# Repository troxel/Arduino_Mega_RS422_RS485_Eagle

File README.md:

# Arduino_Mega_RS422_RS485_Eagle

## Eagle files for a shield for Arduinio Mega providing both RS422 and RS485 ports

Usess ttl uarts 1 and 2 to provide both RS485 and RS422 level ports. The RS485 requires setting GPIO pin 7 high to enable output and suppress imput.

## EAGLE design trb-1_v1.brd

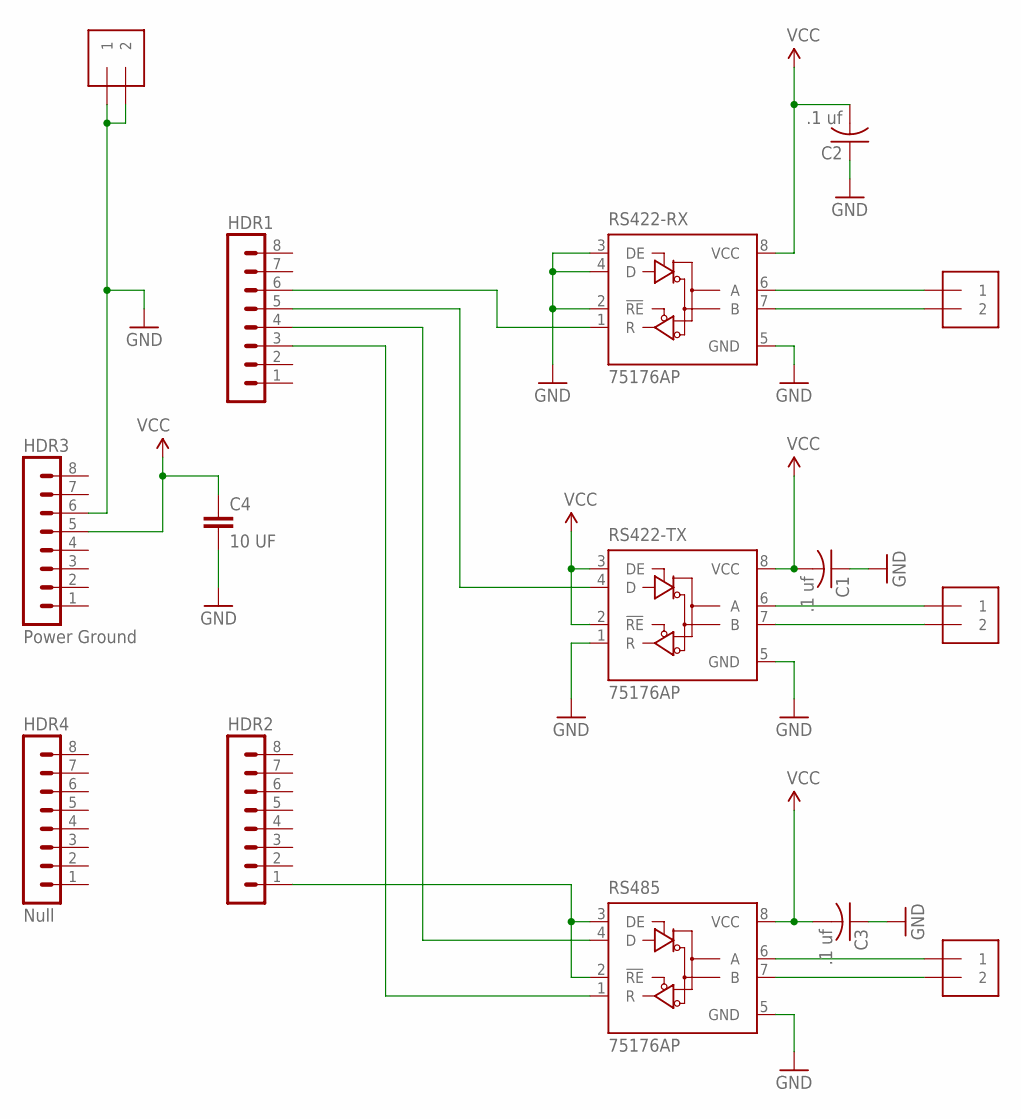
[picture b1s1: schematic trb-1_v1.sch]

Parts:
C1, C2, C3: .1 uf; C0805
C4: 10 UF; 0805-CAP
HDR1, HDR2: MA08-1
HDR3: Power Ground; MA08-1
HDR4: Null; MA08-1
J1: 1X2-3.5MM
RS422-RX, RS422-TX, RS485: 75176AP; DIL08; MPN SN75176AP
RS422-RX1, RS422-TX1, RS485-TXRX: 1X2-3.5MM

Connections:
GND: C1.1, C2.1, C3.1, C4.2, HDR3.6, J1.1, J1.2, RS422-RX.2 (!RE), RS422-RX.3 (DE), RS422-RX.4 (D), RS422-RX.5 (GND), RS422-TX.1 (R), RS422-TX.5 (GND), RS485.5 (GND)
unnamed: HDR1.3, RS485.1 (R)
unnamed: HDR1.4, RS485.4 (D)
unnamed: HDR1.5, RS422-TX.4 (D)
unnamed: HDR1.6, RS422-RX.1 (R)
unnamed: HDR2.1, RS485.2 (!RE), RS485.3 (DE)
unnamed: RS422-RX.6 (A), RS422-RX1.1
unnamed: RS422-RX.7 (B), RS422-RX1.2
unnamed: RS422-TX.6 (A), RS422-TX1.1
unnamed: RS422-TX.7 (B), RS422-TX1.2
unnamed: RS485.6 (A), RS485-TXRX.1
unnamed: RS485.7 (B), RS485-TXRX.2
VCC: C1.2, C2.2, C3.2, C4.1, HDR3.5, RS422-RX.8 (VCC), RS422-TX.2 (!RE), RS422-TX.3 (DE), RS422-TX.8 (VCC), RS485.8 (VCC)

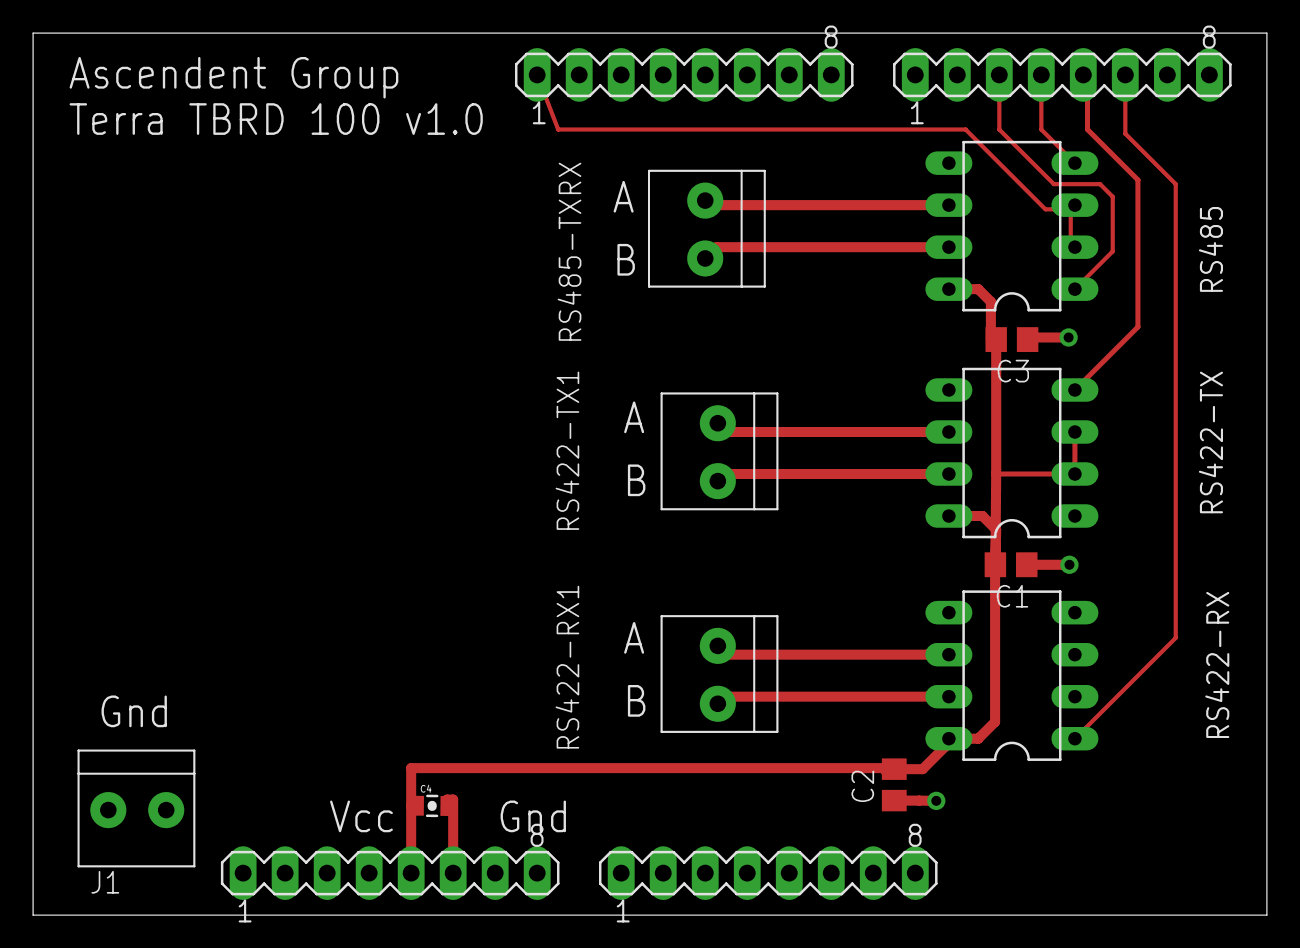
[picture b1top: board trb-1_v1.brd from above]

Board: 2 copper layers, 74.6 x 53.3 mm, 15 parts (0 on the bottom side), 13 nets.

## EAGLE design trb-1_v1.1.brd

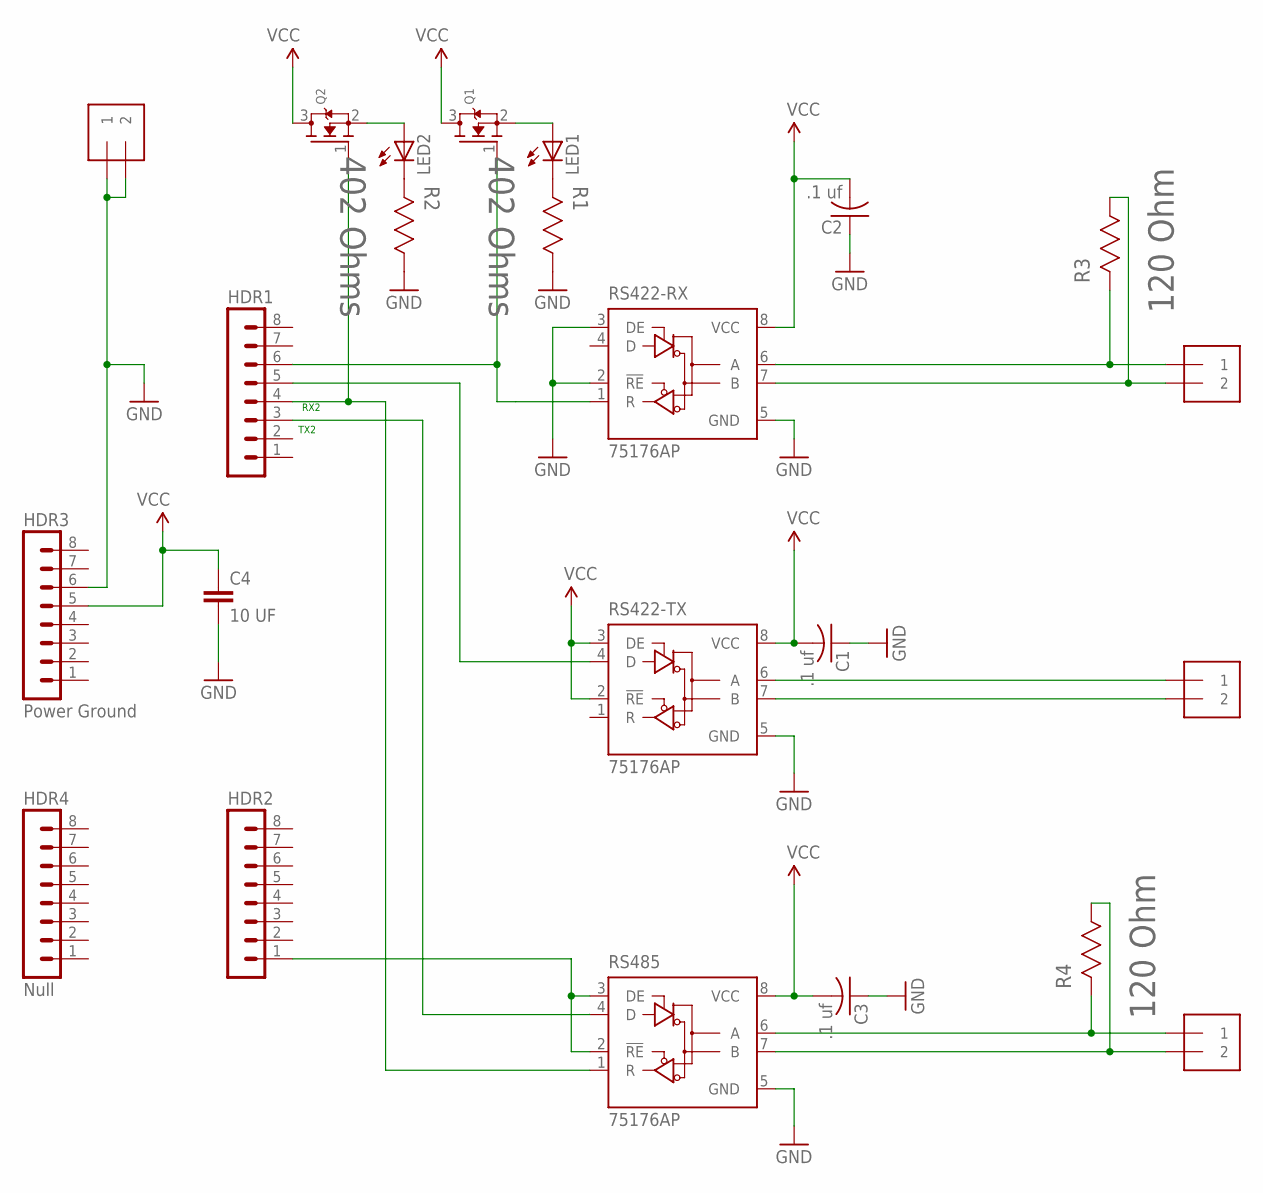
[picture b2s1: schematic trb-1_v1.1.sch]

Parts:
C1, C2, C3: .1 uf; C0805
C4: 10 UF; 0805-CAP
HDR1, HDR2: MA08-1
HDR3: Power Ground; MA08-1
HDR4: Null; MA08-1
J1: 1X2-3.5MM
LED1, LED2: LEDCHIP-LED0805; CHIP-LED0805
Q1, Q2: MOSFET-NREFLOW; SOT23
R1, R2: 402 Ohms; RESC2013X65N
R3, R4: 120 Ohm; RESC2013X65N
RS422-RX, RS422-TX, RS485: 75176AP; DIL08; MPN SN75176AP
RS422-RX1, RS422-TX1, RS485-TXRX: 1X2-3.5MM

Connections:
GND: C1.1, C2.1, C3.1, C4.2, HDR3.6, J1.1, J1.2, R1.1 (R1), R2.1 (R1), RS422-RX.2 (!RE), RS422-RX.3 (DE), RS422-RX.5 (GND), RS422-TX.5 (GND), RS485.5 (GND)
unnamed: HDR1.4, Q2.1 (G), RS485.1 (R)
unnamed: HDR1.3, RS485.4 (D)
unnamed: HDR1.5, RS422-TX.4 (D)
unnamed: HDR1.6, Q1.1 (G), RS422-RX.1 (R)
unnamed: HDR2.1, RS485.2 (!RE), RS485.3 (DE)
unnamed: R3.2 (R2), RS422-RX.6 (A), RS422-RX1.1
unnamed: R3.1 (R1), RS422-RX.7 (B), RS422-RX1.2
unnamed: RS422-TX.6 (A), RS422-TX1.1
unnamed: RS422-TX.7 (B), RS422-TX1.2
unnamed: R4.2 (R2), RS485.6 (A), RS485-TXRX.1
unnamed: R4.1 (R1), RS485.7 (B), RS485-TXRX.2
unnamed: LED1.C, R1.2 (R2)
unnamed: LED2.A, Q2.2 (S)
unnamed: LED1.A, Q1.2 (S)
unnamed: LED2.C, R2.2 (R2)
VCC: C1.2, C2.2, C3.2, C4.1, HDR3.5, Q1.3 (D), Q2.3 (D), RS422-RX.8 (VCC), RS422-TX.2 (!RE), RS422-TX.3 (DE), RS422-TX.8 (VCC), RS485.8 (VCC)

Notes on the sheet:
TX2
RX2

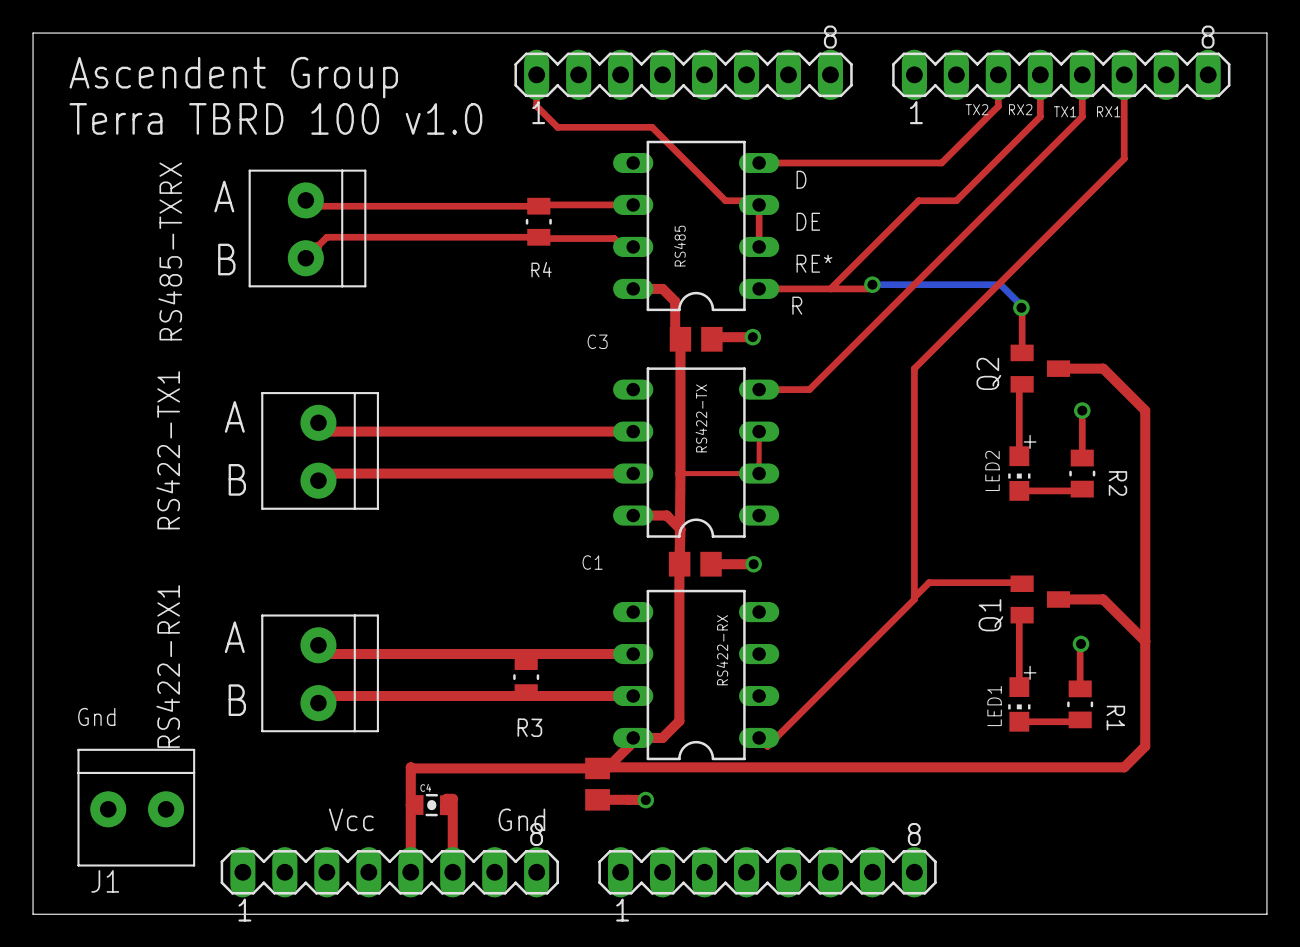
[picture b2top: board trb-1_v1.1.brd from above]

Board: 2 copper layers, 74.7 x 53.3 mm, 23 parts (0 on the bottom side), 17 nets.

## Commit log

2016-02-28 Init of Arduino mega shield with RS422 and RS485

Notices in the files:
parts and their libraries:
SparkFun-Capacitors: Licensing: Creative Commons ShareAlike 4.0 International - https://creativecommons.org/licenses/by-sa/4.0
